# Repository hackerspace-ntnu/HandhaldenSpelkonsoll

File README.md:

# Handhalden Spelkonsoll
  
Dette er et prosjekt med mål om å utvikle en håndholdt spillkonsoll basert på ESP32 og skjermkontrolleren ILI9488.  
Spillkonsollen kommer med et egetutviklet snake-spill.
  
# Features som er planlagt og i utvikling:  
#### Hardware:  
* mikrokontroller: ESP32 dev board
* skjerm: ILI9488 480*320, 3.5"  
* input: Dpad + 4 knapper
* kretskort: [custom KiCad modell](hardware/kretskort/)  
* kabinett: 3d printet, [cad filer](hardware/design/) følger og det er åpent for tilpassing som i valg av farger

#### Software:  
* Spill: snake  
* Grafikk: [LVGL](https://github.com/lvgl/lvgl)
* ~~Kommunikasjonsprotokoll: [ESP-NOW](https://github.com/espressif/esp-now)~~

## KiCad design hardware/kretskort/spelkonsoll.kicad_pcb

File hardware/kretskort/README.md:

# kretskort

## TODO
- [ ] Fikse pull-up/down resistor (ikke ha en wack kombo av begge)
- [ ] Snu ESP-en, så usben ikke krasjer med resistorene
- [ ] Fjerne de knappene vi ikke trenger/ikke kan ha, pin 5-12 var muligens problematisk, flere kan også være det
- [ ] Finne riktige pins til skjermen
- [ ] Route på nytt

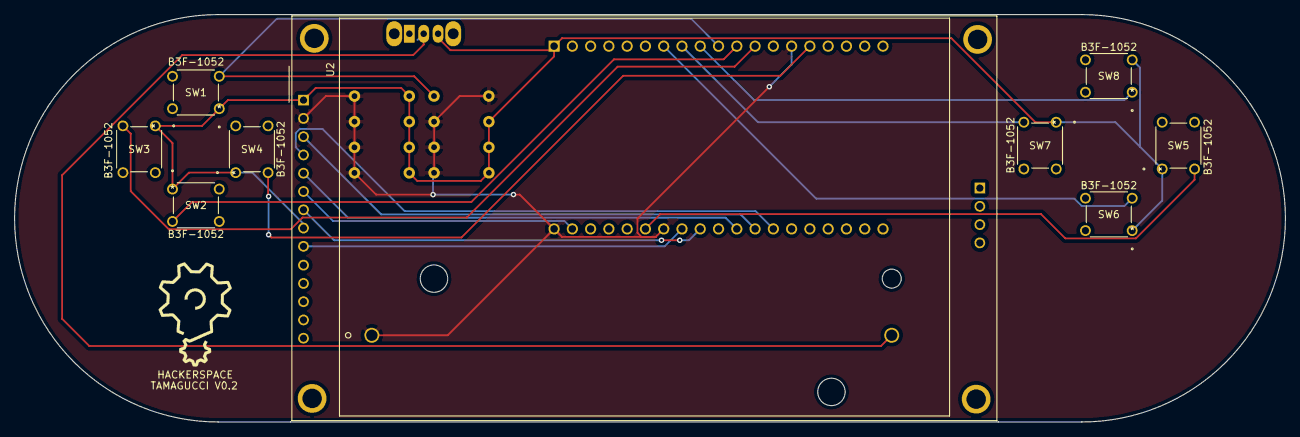
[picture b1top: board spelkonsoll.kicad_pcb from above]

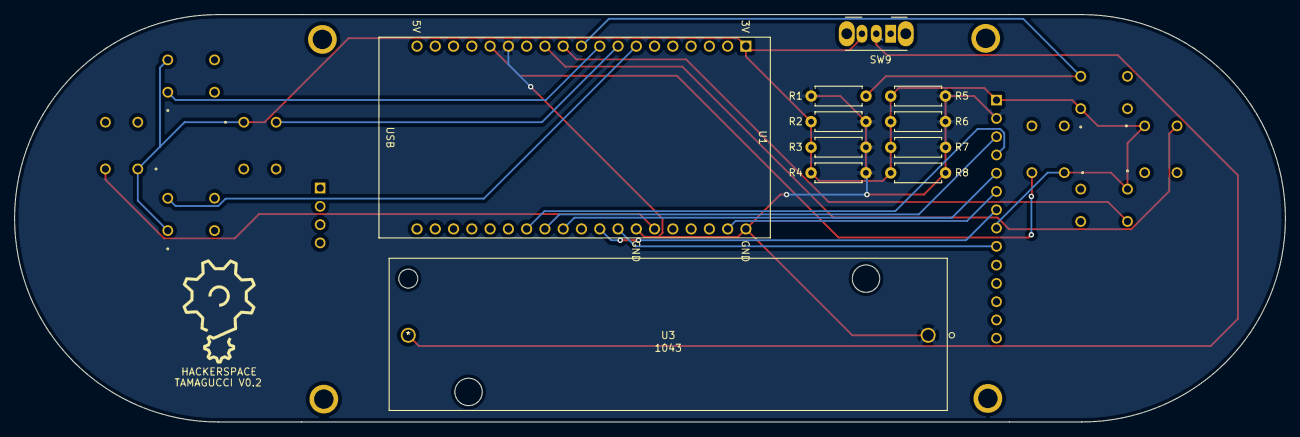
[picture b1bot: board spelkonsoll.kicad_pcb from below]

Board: 2 copper layers, 176.6 x 56.6 mm, 20 parts (11 on the bottom side), 17 nets.

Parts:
R1, R2, R3, R4, R5, R6, R7, R8: 10K; R_Axial_DIN0207_L6.3mm_D2.5mm_P7.62mm_Horizontal
SW1, SW2, SW3, SW4, SW5, SW6, SW7, SW8: B3F-1052; Button
SW9: SW_DPDT_x2; PowerButton
U1: ESP32-DEVKITC-32D; MODULE_ESP32-DEVKITC-32D
U2: ILI9488
U3: 1043; 18650holder

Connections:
+5V: R2.1, R3.1, R4.1, R5.1, R6.1, R7.1, R8.1, SW1.1, SW2.1, SW3.1, SW4.1, SW5.1, SW6.1, SW7.1, SW8.3, SW9.3, U1.1, U2.1, U2.8
BTN_A: SW5.3, U1.25
BTN_B: SW6.3, U1.7
BTN_DP_DOWN: SW2.3, U1.11
BTN_DP_LEFT: SW3.3, U1.12
BTN_DP_RIGHT: SW4.3, U1.15
BTN_DP_UP: R1.1, SW1.3, U1.10
BTN_X: SW7.3, U1.8
BTN_Y: SW8.1, U1.9
CS: U1.31, U2.3
DC\RS: U1.30, U2.5
GND: R1.2, R2.2, R3.2, R4.2, R5.2, R6.2, R7.2, R8.2, U1.14, U1.20, U1.26, U2.2, U3.1
MISO: U1.27, U2.9
MOSI: U1.21, U2.6
unnamed: SW9.2, U3.2
RESET: U1.32, U2.4
SCK: U1.28, U2.7

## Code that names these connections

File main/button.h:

#include <stdio.h>
#include <string.h>
#include <stdlib.h>
#include <inttypes.h>
#include "freertos/FreeRTOS.h"
#include "freertos/task.h"
#include "freertos/queue.h"
#include "driver/gpio.h"

#ifndef BUTTON_H
#define BUTTON_H


#define BTN_DP_RIGHT  GPIO_NUM_13
#define BTN_DP_LEFT  GPIO_NUM_14     
#define BTN_DP_DOWN  GPIO_NUM_27  
#define BTN_DP_UP GPIO_NUM_26 
#define BTN_A  GPIO_NUM_21
#define BTN_B  GPIO_NUM_32 
#define BTN_X  GPIO_NUM_33 
#define BTN_Y  GPIO_NUM_25

//gpio_num_t button_pins[8] = {BTN_DP_RIGHT, BTN_DP_DOWN, BTN_DP_LEFT, BTN_DP_UP, BTN_A, BTN_B, BTN_X, BTN_Y};

//void init_buttons();
//int read_button(gpio_num_t pin);

#endif

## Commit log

2021-10-22 prosjektmapper
2021-10-29 startet på en oversikt over hardvare
2021-10-29 Added compilation instructions
2021-10-29 Added main from old repo
2021-11-04 combined keypress for all platforms
2021-11-04 removed some comments and added some code for windows
2021-11-04 Made basic header file for board
2021-11-04 Created more board functions
2021-11-04 all control paths covered
2021-11-04 Starting to put stuff together
2021-11-04 Fixed errors, everything compiles and runs now at least :D
2021-11-05 Added some logic for eating and placing food
2021-11-05 Another approach for making keypresses in windows work
2021-11-11 Created print board function, and cleaned up some code
2021-11-12 added boilerplate for ILI9488 screen
2021-11-12 moved from Arduino IDE to VS Code
2021-11-12 removed comments
2021-11-13 included keypress code in board.c
2021-11-15 updated boilerplate, now includes snake-movement
2021-11-18 changed order of drawing
2021-11-18 Updated README.md
    start description of what the project is about
2021-11-18 Update README.md
    Added TODOs
2021-11-19 renamed files and modified width and height
2021-11-19 added changes from mush_it_all_together
2021-11-19 cleanup
2021-11-20 width and heigth are now correct
2022-01-18 break snake.ino
    a feature update towards snake game, with braking bugs.
2022-01-21 Did some fixes in movement code
2022-01-21 Forgot to add function in header file
2022-01-21 Implementerte wrapping når slangen går utenfor brettet
2022-01-21 Added some comments
2022-01-21 less borked
2022-01-21 Revert "Merge pull request #6 from hackerspace-ntnu/breaking-bugs"
    This reverts commit ed38c7cc75b39383f745835ec1b95d62ce8576a4, reversing
    changes made to d7784d193c5db177fd8717dea56e7ca7cde7d8dc.
2022-01-25 Splitting a snake now works! :D
2022-01-25 added design file
    a redesign in openscad
2022-01-25 fix typo
    fixed a typo in line 69
2022-01-28 New food will only appear if there is no other food on the board
2022-01-28 Splitting by the head now kills the snake
2022-01-28 Can now add and control multiple snakes on one board
2022-02-04 circuit board kicad files
2022-02-04 Commented out header files
2022-02-04 Started creating main game loop
2022-02-04 added main body
    added the rest of holes and started work on the outer shell.
2022-02-11 Raw pain
2022-02-11 Raw bliss
2022-02-11 more circuit board kicad files
2022-02-17 added the stl file from deisgn group
2022-02-17 modified pcb to fit new design
2022-02-17 fixed DRC error
2022-02-18 Create test_topology
2022-02-25 Fixed parameter to match function
2022-02-25 Added semaphores
2022-02-25 Progress so far. Will crash :c
2022-02-25 added power circuit
2022-02-25 lol glemte å lagre
2022-03-04 IT WORKS
2022-03-04 Snake now increases in size when splitting another
2022-03-04 Made contant to monitor food amount
2022-03-04 Set up simple snake game
2022-03-04 Got rid of comments related to semafores and threads
2022-03-11 added pinouts between ILI9488 and ESP32
2022-03-16 Sneks can now eat each other omnomnom
2022-03-16 la til gerber filer fra forrige gang
2022-03-16 added custom library files
2022-03-16 modified buttons to maybe work
2022-03-16 lol glemte å lagre igjen
2022-03-18 Snek can now commit die.
2022-03-18 Fixed food shortage and set up for more snakes
2022-03-18 Fixed food shortage
2022-03-23 Made simple multiplayer example
2022-03-23 Implemented out of bounds more tailored for current code condition
2022-03-23 Made attempt at multiplayer specific struct
2022-03-23 Snake-adding simplified while
2022-03-25 -1 is now less than 0; i.e, implemented BoardPiece structs to keep piece types and body pointers
2022-03-25 Minor syntax changes, and removed some unused code
2022-03-26 added new gerber files
2022-03-26 added modified files for new circuit
2022-04-01 Added boundary checks for getting and setting board values
2022-04-01 start setting up for multiplayer
2022-04-01 experimental function to get info from other consoles
2022-04-06 Cleaned up after merge. Snake game should be operative
2022-04-06 Alternate key input method
2022-04-22 started on v0.2 moved resistors and added silkscreen for inputs on the ESP32
2022-04-22 Fixed bugs that made snakes self cannibalize and duplicate limbs
2022-04-22 Changed some values for easier debugging
2022-04-22 Commented out some multiplayer details for easier debugging
2022-09-23 added .vscode and build
2022-09-28 added header guards and removed unnecessary includes
2022-09-28 more header files corrections, now able to compile and upload to the esp32
2022-09-28 renamed the .ino file, and copied the main function to game.ino
2022-09-29 added README.md
2022-10-07 added BLOCK_SIZE to constants, now able to draw some snake action. And got rid of obsolete config files
2022-10-08 new communication protocol; ESP-NOW
2022-10-08 New communication protocol
2022-10-08 Deleted painlessmesh files, and the howto-file
2022-10-08 added some code for 2-way communication
2022-10-13 Added schema from v0.1, deleted buttons
    Moved resistors and deleted start, select, and shoulder buttons
2022-10-14 the slave prints out the mac-address of master
2022-10-21 updated the hardware file
2022-10-27 deleted example, and updated master and slave
2022-10-27 added function to print MAC-address
2022-11-03 added task in README.md
2022-11-03 added packages3d to gitignore
2022-11-03 update KiCad files
2022-11-04 added new error
2022-11-06 smaller headers in oversikt.md
2022-11-06 added button connections
2022-11-06 updated links in readme
2022-11-06 changed header and removed space
2022-11-07 readme now reflects what we are working on
2022-11-07 same specs in both readme and overview
2022-11-07 small change
2022-11-11 added folder for design related stuff
2022-11-11 deleted .gitkeep files
2022-11-11 rewrite description of project
2022-11-13 commented out multiplayer stuff, and removed draw_grid function
2022-11-14 update schematic and footprints
2022-11-15 added descriptive comments and changed variable type for the mac-address
2022-11-15 starting to combine master and slave code so that only on sketch need to be uploaded to the ESP
2022-11-15 style changes and now the dummy peer gets deleted after a connection is made
2022-11-16 simplify, renameing and commments
2022-11-16 deleted master and slave
2022-11-18 refactoring and comments
2022-11-19 hopefully it works now, might test later idk
2022-11-19 deleted .vscode
2022-11-21 renamed old gerbers and added new symbols
2022-11-21 added power switch
2023-01-10 getting ready to switch from arduino to espressif
2023-01-20 deleted master and slaveand added the espnow-example from esp-idf
2023-01-21 removed arduino stuff, commented out some functions which could be useful later on.
2023-01-22 project now uses ESP-IDF
2023-01-22 added sdkconfig to gitignore
2023-01-22 deleted obsolete files and moved the multiplayer function to main
2023-01-22 addded components folder
2023-01-22 moved espnow-files to main folder
2023-01-23 renamed espnow files and did some style changes
2023-01-24 glemte å lagre :(
2023-01-25 updated cmakelists
2023-01-25 undo changes in cmakelists.txt
2023-01-25 removed sdkconfig
2023-01-25 added button files and tested it in the game loop
2023-01-26 modified espnow example
2023-01-26 renamed files
2023-01-26 added a config file
2023-01-26 renamed
2023-01-26 added comms.c to CMakeLists
2023-01-26 renamed config title and moved defines to header
2023-01-26 removed some comments
2023-01-28 added config fo espnow
2023-01-28 created new files for our multiplayer stuff
2023-01-28 added multiplayer.c to CMakeLists
2023-01-28 minor changes to main and comms
2023-01-28 i regret this
2023-01-28 I'll give it a try
2023-01-28 going to try 1D array for the board
2023-01-28 I think it should work now
2023-01-29 moved all types to new file reduced includes everywhere
2023-01-29 undo changes in main, getting ready to merge
2023-01-29 ready to merge
2023-01-29 gerbers_v0.2
2023-01-29 må slutte å glemme å lagre :(
2023-01-30 it works in my machine
2023-01-31 adede lvgl and drivers
2023-02-03 f*ck yeah, it compiles
2023-02-04 it still works, managed to get rid of lvgl
2023-02-04 deleted driver folder and moved all .h files into seperate folder
2023-02-06 changes to it make work
2023-02-08 added lvgl and drivers as a idf-component.
2023-02-08 slight changes in the drivers, deleted submodules
2023-02-09 moved lvgl into componentns folder
2023-02-12 code for lvgl callbacks
2023-02-17 small change (jk)
2023-02-19 removed duplicate includes
2023-02-21 removed unused code, keeping some config for similar display drivers
2023-02-21 added default values in Kconfig and removed includes for drivers we don't have
2023-02-21 now the correct default values are chosen
2023-02-21 changed the pinout
2023-02-21 deleted some stuff
2023-02-21 deleted more stuff
2023-02-22 commented out printf because it interferes with the drawing, also removed som empty space in main
2023-02-22 removed static keyword
2023-02-24 changed text color
2023-02-25 removed merging-stuff, and commented out a function
2023-02-25 merge/reverting fix
2023-04-18 it suddenly works
2023-04-18 fixes
2023-04-21 started on some gfx action
2023-04-22 Changed constant to make the testing simpler
2023-04-22 Working graphic for the first frame
2023-04-22 Changed amount of players to 1 for testing purposes
2023-05-05 Moved commented out code to main
2023-05-05 Updated a constant
2023-05-05 voerging snake
2023-05-06 Working snake
2023-05-22 upload case files

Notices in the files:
parts and their libraries:
Copyright 2021 Accelerated Designs. All rights reserved.
